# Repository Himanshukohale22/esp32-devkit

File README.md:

## ESP32-devkit

Hardware files for esp32-devkit

### Specification
---
* ESP32 wroom 32 onboard microcontroller.
* High operating frequency.
* fast and reliable with low power supply.
* Blutooth and wifi availability.
* power supply
    * usb b mini 
    * Vin pin (3.5-12v)
* consist of GPIO's,I2c,SPI,UART communicaton protocols.
* ESP32 Wroom is SOC with wifi and Bluetooth capabilities.

Plots
----

3D render

Top

Bottom

Tools & Referances

- [kiCad](https://www.kicad.org/)
- [ESP32 datasheet](https://www.espressif.com/sites/default/files/documentation/esp32-wroom-32_datasheet_en.pdf)

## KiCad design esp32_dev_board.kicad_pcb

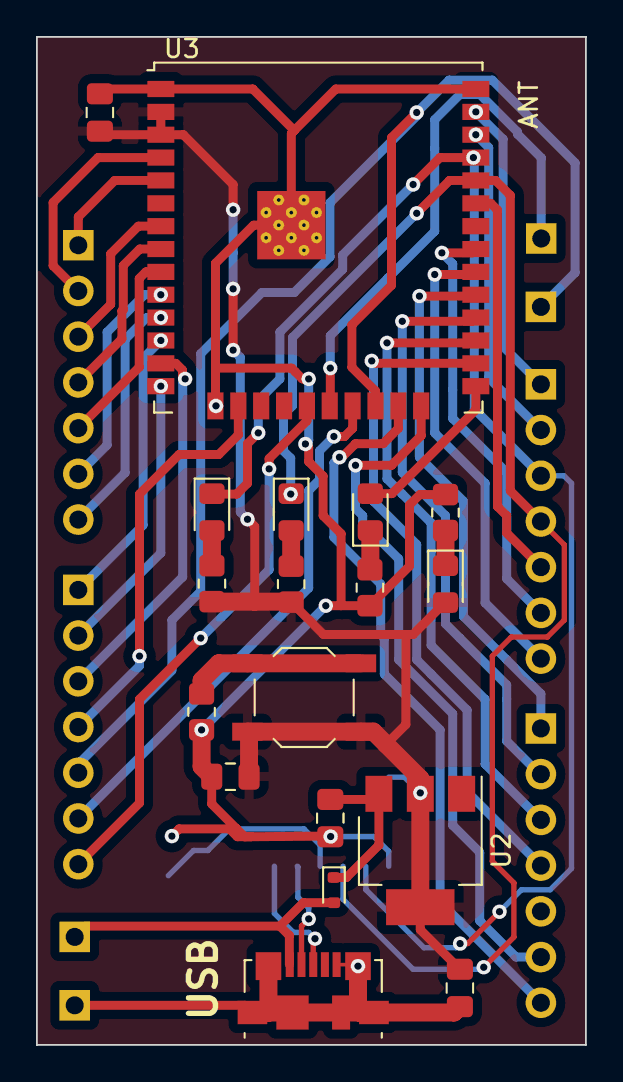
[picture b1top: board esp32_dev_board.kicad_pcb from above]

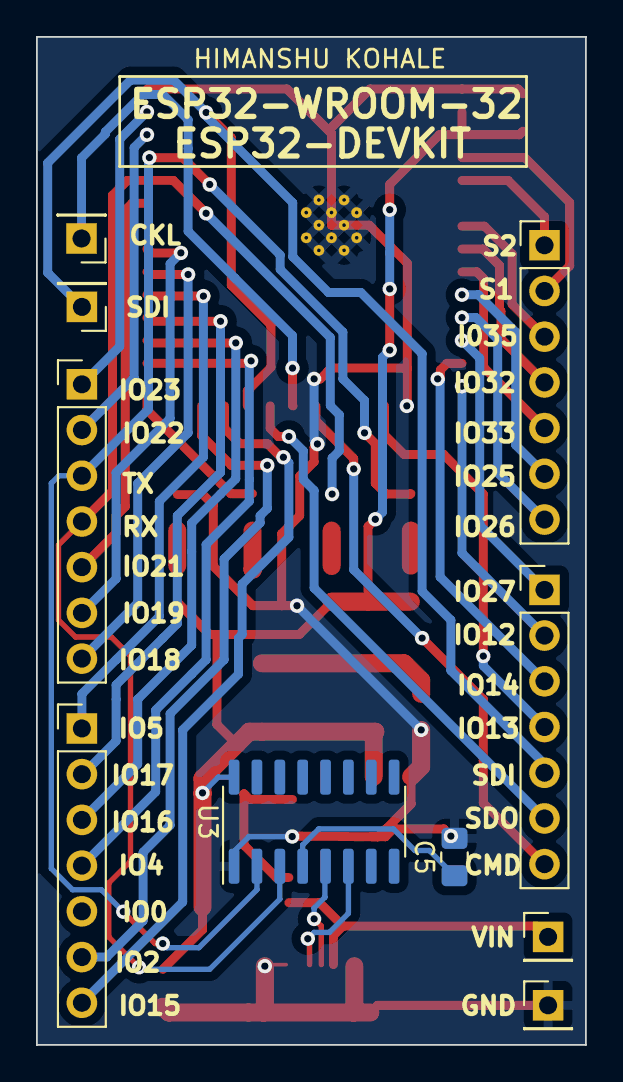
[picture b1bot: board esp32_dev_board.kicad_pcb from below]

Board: 2 copper layers, 30.5 x 56.0 mm, 28 parts (10 on the bottom side), 41 nets.

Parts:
C1, C2: 100nf; C_0805_2012Metric_Pad1.18x1.45mm_HandSolder
C3: 10uf; C_0805_2012Metric_Pad1.18x1.45mm_HandSolder
C4, C5: 0.1uf; C_0805_2012Metric_Pad1.18x1.45mm_HandSolder
D1, D2, D5, D6: LED; LED_0805_2012Metric_Pad1.15x1.40mm_HandSolder
D4: 1N914WT; D_SOD-523
J1, J5, J6, J7: Conn_01x07_Pin; PinHeader_1x07_P2.54mm_Vertical
J2, J4, J8, J9: Conn_01x01_Pin; PinHeader_1x01_P2.54mm_Vertical
J3: USB_B_Mini; USB_Micro-B_Molex_47346-0001
R1, R3, R4, R5: 1k; R_0805_2012Metric_Pad1.20x1.40mm_HandSolder
R2: 4.7k; R_0805_2012Metric_Pad1.20x1.40mm_HandSolder
SW1: SW_SPST; SW_SPST_TL3342
U2: AMS1117-3.3; SOT-223-3_TabPin2
U3: ESP32-WROOM-32U
U3#2: CH340C; SOIC-16_3.9x9.9mm_P1.27mm

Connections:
3.3v: C1.1, C2.1, C4.1, D6.2 (A), R1.2, R3.2, SW1.2 (B), U2.2 (VO), U3.2 (VDD), U3.3 (EN), U3#2.16 (VCC)
CLK: J2.1, U3.20 (SCK/CLK)
CMD: J5.7, U3.19 (SCS/CMD)
GND: C1.2, C2.2, C3.2, C4.2, C5.2, J3.5 (GND), J3.6 (Shield), J9.1, R2.1, R4.2, R5.2, U3.1 (GND), U3.15 (GND), U3.38 (GND), U3.39 (GND), U3#2.1 (GND)
IO2: J7.6, U3.24 (IO2)
IO4: J7.4, U3.26 (IO4)
IO5: J7.1, U3.29 (IO5)
IO12: J5.2, U3.14 (IO12)
IO13: J5.4, U3.16 (IO13)
IO14: J5.3, U3.13 (IO14)
IO15: J7.7, U3.23 (IO15)
IO16: J7.3, U3.27 (IO16)
IO17: J7.2, U3.28 (IO17)
IO18: J6.7, U3.30 (IO18)
IO19: J6.6, U3.31 (IO19)
IO21: J6.5, U3.33 (IO21)
IO22: J6.2, U3.36 (IO22)
IO23: J6.1, U3.37 (IO23)
IO25: J1.6, U3.10 (IO25)
IO26: J1.7, U3.11 (IO26)
IO27: J5.1, U3.12 (IO27)
IO32: J1.4, U3.8 (IO32)
IO33: J1.5, U3.9 (IO33)
IO35: J1.3, U3.7 (IO35)
LED: D5.2 (A), U3.25 (IO0)
unnamed: D1.2 (A), R1.1
unnamed: D2.2 (A), R3.1
unnamed: C3.1, D4.1 (K), U2.3 (VI)
unnamed: D5.1 (K), R4.1
unnamed: D6.1 (K), R5.1
unnamed: R2.2, SW1.1 (A)
unnamed: C5.1, U3#2.4 (V3)
RX_MCU: D2.1 (K), J6.4, U3.34 (RXD0/IO3), U3#2.3 (RXD)
SDI: J5.5, J8.1, U3.22 (SDI/SD1)
SDO: J5.6, U3.21 (SDO/SD0)
SENSRO1: J1.2, U3.4 (SENSOR_VP)
SENSRO2: J1.1, U3.5 (SENSOR_VN)
TX_MCU: D1.1 (K), J6.3, U3.35 (TXD0/IO1), U3#2.2 (TXD)
USB_M: J3.2 (D-), U3#2.5 (UD+)
USB_P: J3.3 (D+), U3#2.6 (UD-)
VBUS: D4.2 (A), J3.1 (VBUS), J4.1

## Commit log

2023-08-23 first uploaded
